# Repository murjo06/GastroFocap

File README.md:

# Gastro Focap INDI driver with firmware

### Installing the INDI driver
```sh
mkdir -p build
cd build
cmake -DCMAKE_INSTALL_PREFIX=/usr -DCMAKE_BUILD_TYPE=Debug ..
make
sudo make install
```

### Uploading the firmware

Upload the [esp32.ino](esp32.ino) file to an ESP32 S3. If your module has PSRAM, you'll have to change the pins, since the PSRAM uses pins 35, 36, and 37 on the S3. The PCB won't work in that case.

Alternatively, you can use an Arduino Nano and upload the [arduino.ino](arduino.ino) file, but this only contains flatcap functionality.

This firmware uses the M24C64 EEPROM IC by default, but that can be changed to use the ESP32 S3's own "EEPROM", although I don't recommend it. Since EEPROM has limited write cycles (to be fair that's about 4 million for the M24C64), it's best to change the exposure length of flats through different filters, rather than changing the brightness value for each filter (for the Arduino version of the firmware this becomes slightly more applicable, since it has only 100000 write cycles). Ekos, as far as I know, doesn't even offer a way to change flatcap brightness in different filters.

The communication protocol requests and responses are located in [communication.md](communication.md).

I've provided gerbers for the PCB inside the [pcb_gerbers](/pcb_gerbers/) folder. You may use these (as well as other files in this repository) as per the [license file](/LICENSE). I recommend using JLCPCB for the manufacturing, since the bom is suited for it. You can leave all settings as default, just make sure to correct all the errors in the pick-and-place file, since there are many. JLCPCB allows you to do that in the website. You'll also need some additional components that aren't in the BOM (rather [here](/pcb_gerbers/additional_bom.md)) and have to be manually soldered since it's cheaper that way.

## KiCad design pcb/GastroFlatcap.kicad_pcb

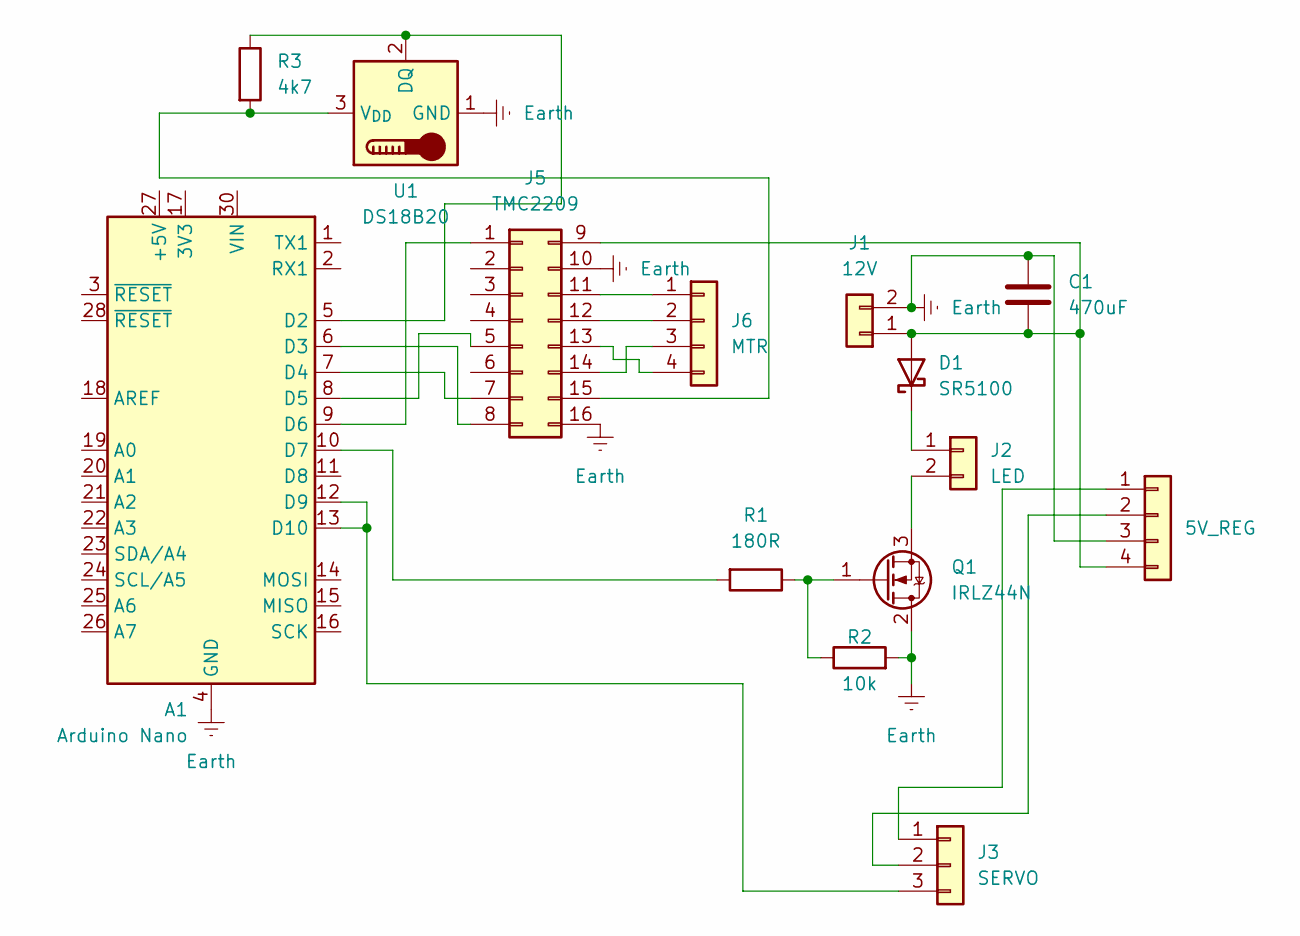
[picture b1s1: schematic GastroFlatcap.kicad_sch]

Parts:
A1: Arduino Nano; Arduino_Nano
C1: 470uF; CP_Radial_D6.3mm_P2.50mm
D1: SR5100; D_DO-27_P15.24mm_Horizontal
J1: 12V; BarrelJack_CUI_PJ-063AH_Horizontal
J2: LED; JST_XH_B2B-XH-A_1x02_P2.50mm_Vertical
J3: SERVO; JST_XH_B3B-XH-A_1x03_P2.50mm_Vertical
J4: 5V_REG; PinHeader_1x04_P6.00mm_Vertical
J5: TMC2209; Pin_Header_02x08_6_spaces_2,50mm
J6: MTR; JST_XH_B4B-XH-A_1x04_P2.50mm_Vertical
Q1: IRLZ44N; TO-220-3_Vertical
R1: 180R; R_Axial_DIN0207_L6.3mm_D2.5mm_P7.62mm_Horizontal
R2: 10k; R_Axial_DIN0207_L6.3mm_D2.5mm_P7.62mm_Horizontal
R3: 4k7; R_Axial_DIN0411_L9.9mm_D3.6mm_P12.70mm_Horizontal
U1: DS18B20; PinHeader_1x03_P2.54mm_Vertical

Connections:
Earth: A1.4 (GND), A1.29 (GND), C1.1, J1.2, J4.3, J5.10, J5.16, Q1.2 (D), R2.2, U1.1 (GND)
unnamed: A1.5 (D2), R3.1, U1.2 (DQ)
unnamed: A1.6 (D3), J5.8
unnamed: A1.7 (D4), J5.7
unnamed: A1.8 (D5), J5.5
unnamed: A1.9 (D6), J5.1
unnamed: A1.10 (D7), R1.2
unnamed: A1.12 (D9), A1.13 (D10), J3.3
unnamed: C1.2, D1.2 (A), J1.1, J4.4, J5.9
unnamed: D1.1 (K), J2.1
unnamed: J2.2, Q1.3 (S)
unnamed: J3.1, J4.1
unnamed: J3.2, J4.2
unnamed: J5.11, J6.1
unnamed: J5.12, J6.2
unnamed: J5.13, J6.4
unnamed: J5.14, J6.3
unnamed: J5.15, R3.2, U1.3 (V_{DD})
unnamed: Q1.1 (G), R1.1, R2.1

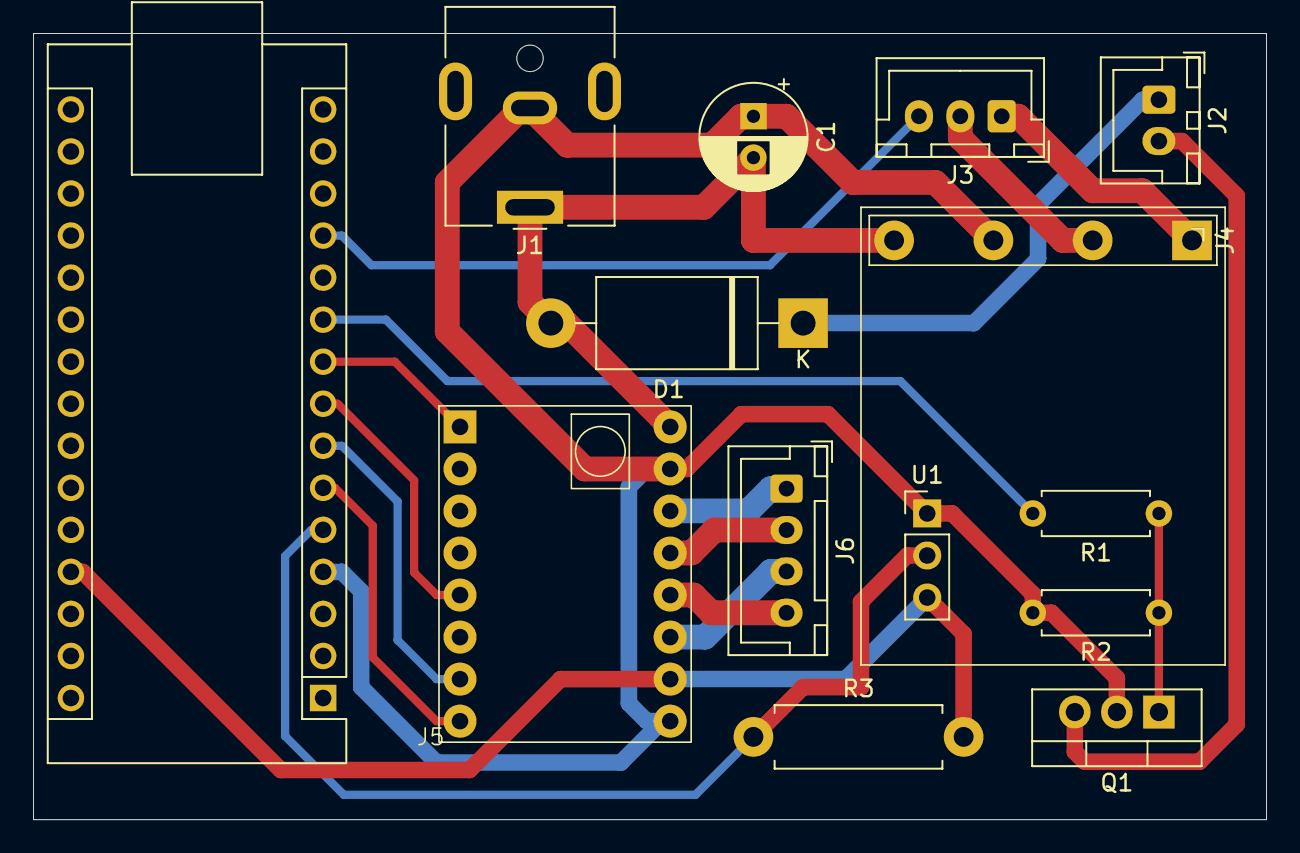
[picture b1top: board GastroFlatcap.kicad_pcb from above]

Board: 2 copper layers, 74.5 x 47.5 mm, 14 parts (0 on the bottom side), 19 nets.

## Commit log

2024-08-03 Added firmware calibration
2024-08-03 Added servo support
2024-08-03 Set LED pin to high-frequency PWM
2024-08-03 Added EEPROM for fail-safe
2024-08-04 Now reports when servo is moving
2024-08-04 Added modified Alnitak flip-flat driver
2024-08-04 Added open/closed shutter options
2024-08-04 Set servo delay to 200
2024-08-04 Used EEPROM more sparingly
2024-08-05 Considers servo speed
2024-08-05 Removed unnecessary EEPROM calls
2024-08-05 Added EEPROM 16-bit int support
2024-08-05 Added get functions for shutter angles in firmware
2024-08-05 Added get shutter angles in driver
2024-08-05 Debugged firmware
2024-08-05 Improved comments
2024-08-05 Made README clearer
2024-08-05 Made firmware less error-prone
2024-08-06 Code cleanup
2024-08-06 EEPROM write debug
2024-08-08 Light only turns on when shutter is closed
2024-08-10 Made brightness 0 or more
2024-08-11 Corrected responses in firmware
2024-08-11 Driver debug
2024-08-11 Driver debug 2
2024-08-11 Driver debug 3
2024-08-11 Set steps to 1
2024-08-11 Debug 4
2024-08-12 Added correct formatting for angles
2024-08-12 Changed MAX_ANGLE and step size
2024-08-12 Removed layer of angle restriction
2024-08-12 Improved firmware
2024-08-12 Firmware removed semicolon from #define
2024-08-12 Fixed sendCommand()
2024-08-12 Raised timeout
2024-08-12 Added firmware command restriction
2024-08-13 Made firmware more reliable
2024-08-13 Better to print in switch case
2024-08-14 Changed brightness to 16 bit
2024-08-14 Raised brightness step
2024-08-15 Added DustCapInterface()
2024-08-15 Moved shutter angle setters to private
2024-08-15 Corrected typos
2024-08-15 Fixed warnings
2024-08-16 Fixed driver not connecting on first try
2025-01-18 Cosmetics
2025-01-25 Fixed >K000 response being too long
2025-01-25 Forced use of mod on limited values
2025-01-26 Better comments
2025-01-26 Fixed connection issues
2025-02-18 Changed servo movement to remove fast impacts
2025-04-06 Added automation script
2025-04-07 Delays, better commends and logging
2025-04-07 Minor changes
2025-04-08 Added busy checks
2025-05-10 Renamed closed to park
2025-05-14 Shutter parks now use eeprom
2025-05-18 Added pcb design
2025-05-20 Changed gitginore
2025-06-04 Moved firmware file
2025-06-06 Used new INDI property names
2025-06-07 Corrected brightness bounds
2025-06-19 Fixed light not turning on
2025-07-31 Changed microcontroller to ESP32 S3, merged flatcap with focuser
2025-07-31 Removed unused command
2025-08-03 Name consistency
2025-08-03 Typos
2025-08-12 Fixed most EPS32 issues
2025-08-13 Fixed timer and i2c interference
2025-08-13 Added EEPROM write control
2025-08-13 Fixed flatcap protocol
2025-08-17 Fixed errors here and there
2025-08-20 Added pcb design, license update
2026-02-28 Better merging between the two devices
2026-03-01 Update cmake_modules
2026-03-01 Fixed compile warning
2026-04-03 A few fixes
2026-04-06 Made stepper stronger, fixed minor bugs
2026-04-06 Removed prev statuses
2026-04-23 Fixed wrong light status
